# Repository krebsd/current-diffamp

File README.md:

# Differential current sense Amplifier - current-diffamp

Differential Amplifier circuit for use in current sensing applications. The circuit is designed to be used in conjunction with an oscilloscope.

## PREFACE
This project and especially its documentation including this README is still in a very early state of development. This document will be updated with further information in the future.

## EDA

* [KiCad](http://kicad-pcb.org) - KiCad EDA is used for the PCB design

## Authors

* **David Krebs** - *Initial work* - [krebsd](https://github.com/krebsd)

## License

<br />This work is licensed under a <a rel="license" href="http://creativecommons.org/licenses/by-sa/4.0/">Creative Commons Attribution-ShareAlike 4.0 International License</a>

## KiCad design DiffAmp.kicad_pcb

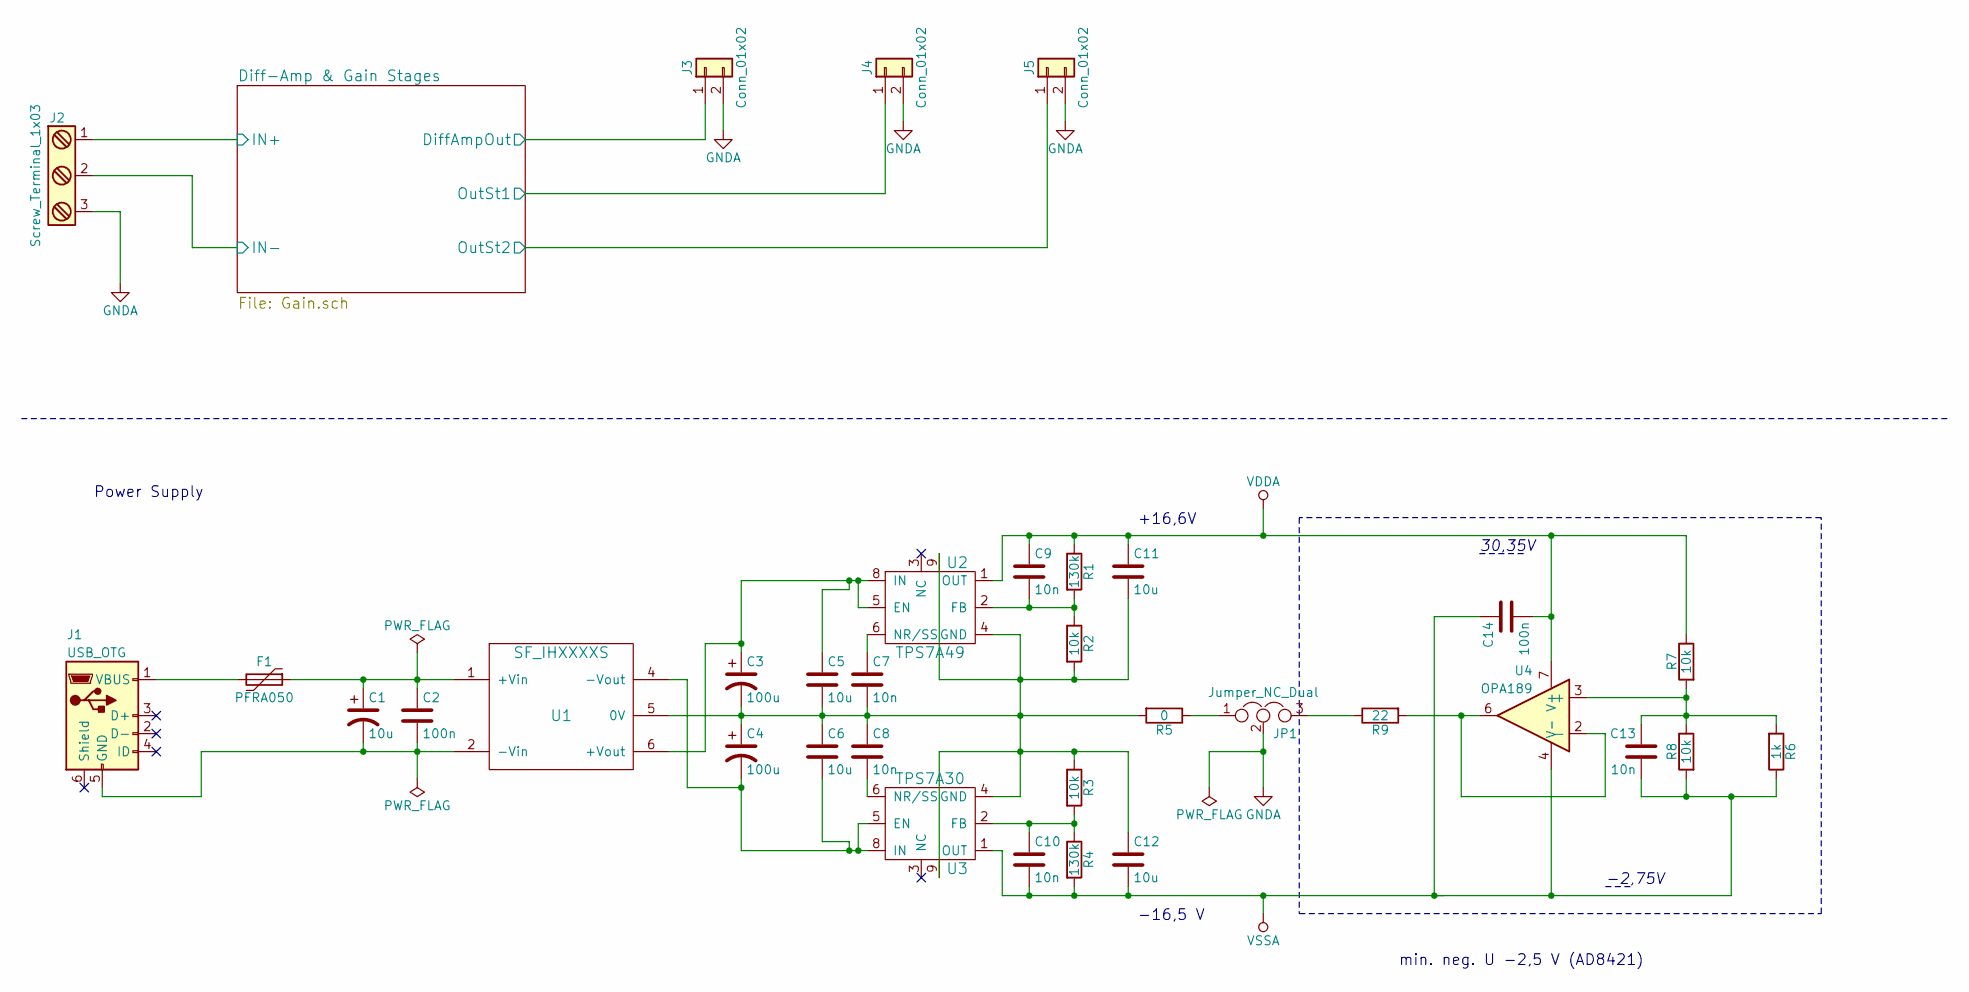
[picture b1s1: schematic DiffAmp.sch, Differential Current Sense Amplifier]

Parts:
C1: 10u; CP_Radial_D5.0mm_P2.00mm
C2, C14: 100n; C_0805
C3, C4: 100u; CP_Radial_D8.0mm_P3.50mm
C5, C6, C11, C12: 10u; C_1210
C7, C8, C9, C10, C13: 10n; C_0805
F1: PFRA050; R_Axial_DIN0204_L3.6mm_D1.6mm_P5.08mm_Horizontal
J1: USB_OTG; MIC_USB_BBU
J2: Screw_Terminal_1x03; TerminalBlock_bornier-3_P5.08mm
J3, J4, J5: Conn_01x02; Pin_Header_Straight_1x02_Pitch2.54mm
JP1: Jumper_NC_Dual; Pin_Header_Straight_1x03_Pitch2.54mm
R1, R4: 130k; R_0805
R2, R3, R7, R8: 10k; R_0805
R5: 0; R_0805
R6: 1k; R_0805
R9: 22; R_0805
U1: SF_IHXXXXS; DCDC-Conv_TRACO_TMR_1-xxxx_Dual
U2: TPS7A49; MSOP-8-1EP_3x3mm_Pitch0.65mm
U3: TPS7A30; MSOP-8-1EP_3x3mm_Pitch0.65mm
U4: OPA189; SOIC-8_3.9x4.9mm_Pitch1.27mm

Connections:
/Diff-Amp & Gain Stages/DiffAmpOut: J3.1; also elsewhere on the board
/Diff-Amp & Gain Stages/IN+: J2.1; also elsewhere on the board
/Diff-Amp & Gain Stages/IN-: J2.2; also elsewhere on the board
/Diff-Amp & Gain Stages/OutSt1: J4.1; also elsewhere on the board
/Diff-Amp & Gain Stages/OutSt2: J5.1; also elsewhere on the board
GNDA: J2.3, J3.2, J4.2, J5.2, JP1.2; also elsewhere on the board
unnamed: C1.1, C2.1, F1.1, U1.1 (+Vin)
unnamed: C1.2, C2.2, J1.5 (GND), U1.2 (-Vin)
unnamed: C3.1, C5.1, U1.6 (+Vout), U2.5 (EN), U2.8 (IN)
unnamed: C4.2, C6.2, U1.4 (-Vout), U3.5 (EN), U3.8 (IN)
unnamed: C7.1, U2.6 (NR/SS)
unnamed: C8.2, U3.6 (NR/SS)
unnamed: C9.2, R1.2, R2.1, U2.2 (FB)
unnamed: C10.1, R3.2, R4.1, U3.2 (FB)
unnamed: C3.2, C4.1, C5.2, C6.1, C7.2, C8.1, C11.2, C12.1, R2.2, R3.1, R5.2, U1.5 (0V), U2.4 (GND), U2.9, U3.4 (GND), U3.9
unnamed: C13.1, R6.2, R7.2, R8.1, U4.3 (+)
unnamed: F1.2, J1.1 (VBUS)
unnamed: JP1.1, R5.1
unnamed: JP1.3, R9.1
unnamed: R9.2, U4.2 (-), U4.6
VDDA: C9.1, C11.1, C14.2, R1.1, R7.1, U2.1 (OUT), U4.7 (V+); also elsewhere on the board
VSSA: C10.2, C12.2, C13.2, C14.1, R4.2, R6.1, R8.2, U3.1 (OUT), U4.4 (V-); also elsewhere on the board

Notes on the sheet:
-16,5 V
+16,6V
-2,75V
30,35V
min. neg. U -2,5 V (AD8421)
Power Supply

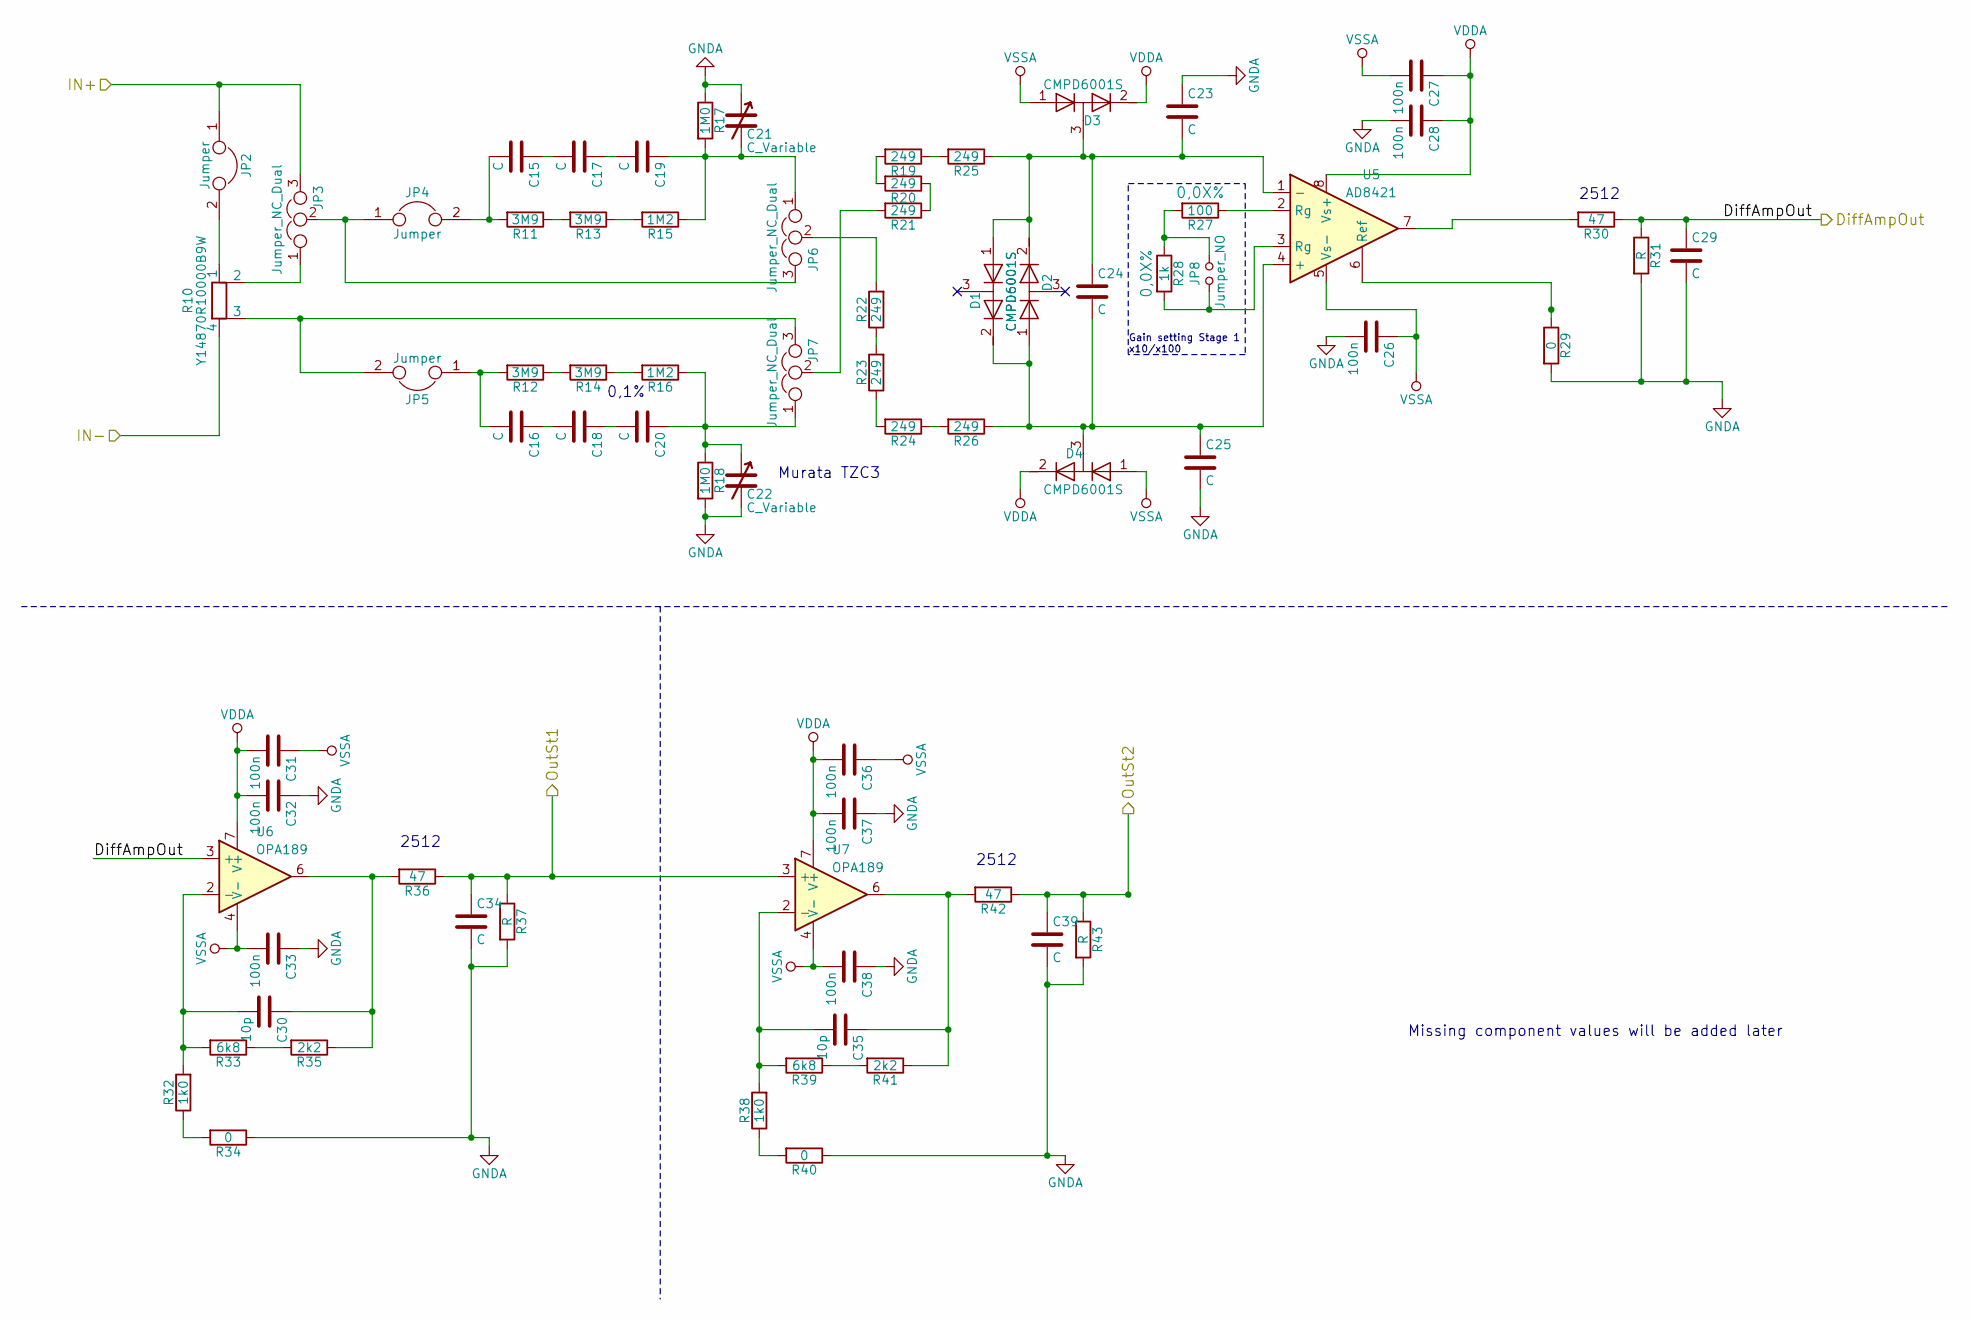
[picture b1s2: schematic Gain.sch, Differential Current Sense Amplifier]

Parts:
C15, C16, C17, C18, C19, C20, C23, C24, C25, C29, C34, C39: C; C_0805
C21, C22: C_Variable; C_Trimmer_Murata_TZC3
C26, C27, C28, C31, C32, C33, C36, C37, C38: 100n; C_0805
C30, C35: 10p; C_0805
D1, D2, D3, D4: CMPD6001S; SOT-23
JP2, JP4, JP5: Jumper; Pin_Header_Straight_1x02_Pitch2.54mm
JP3, JP6, JP7: Jumper_NC_Dual; Pin_Header_Straight_1x03_Pitch2.54mm
JP8: Jumper_NO; Pin_Header_Straight_1x02_Pitch2.54mm
R10: Y14870R10000B9W; CSM2512
R11, R12, R13, R14: 3M9; R_0805
R15, R16: 1M2; R_0805
R17, R18: 1M0; R_0805
R19, R20, R21, R22, R23, R24, R25, R26: 249; R_0805
R27: 100; R_0805; Toleranz 0,0X%
R28: 1k; R_0805; Toleranz 0,0X%
R29, R34, R40: 0; R_0805
R30, R36, R42: 47; R_2512
R31, R37, R43: R; R_0805
R32, R38: 1k0; R_0805
R33, R39: 6k8; R_0805
R35, R41: 2k2; R_0805
U5: AD8421; SOIC-8_3.9x4.9mm_Pitch1.27mm
U6, U7: OPA189; SOIC-8_3.9x4.9mm_Pitch1.27mm

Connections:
/Diff-Amp & Gain Stages/DiffAmpOut: C29.1, R30.1, R31.1, U6.3 (+); also elsewhere on the board
/Diff-Amp & Gain Stages/IN+: JP2.1, JP3.3; also elsewhere on the board
/Diff-Amp & Gain Stages/IN-: R10.4; also elsewhere on the board
/Diff-Amp & Gain Stages/OutSt1: C34.1, R36.1, R37.1, U7.3 (+); also elsewhere on the board
/Diff-Amp & Gain Stages/OutSt2: C39.1, R42.1, R43.1; also elsewhere on the board
GNDA: C21.1, C22.2, C23.1, C25.2, C26.2, C28.2, C29.2, C32.1, C33.1, C34.2, C37.1, C38.1, C39.2, R17.1, R18.2, R29.2, R31.2, R34.1, R37.2, R40.1, R43.2; also elsewhere on the board
unnamed: C15.1, C17.2
unnamed: C15.2, JP4.2, R11.2
unnamed: C16.1, C18.2
unnamed: C16.2, JP5.1, R12.2
unnamed: C17.1, C19.2
unnamed: C18.1, C20.2
unnamed: C19.1, C21.2, JP6.1, R15.1, R17.2
unnamed: C20.1, C22.1, JP7.1, R16.1, R18.1
unnamed: C23.2, C24.1, D1.1 (A), D2.2 (K), D3.3 (common), R25.1, U5.1 (-)
unnamed: C24.2, C25.1, D1.2 (K), D2.1 (A), D4.3 (common), R26.1, U5.4 (+)
unnamed: C30.1, R35.1, R36.2, U6.6
unnamed: C30.2, R32.2, R33.2, U6.2 (-)
unnamed: C35.1, R41.1, R42.2, U7.6
unnamed: C35.2, R38.2, R39.2, U7.2 (-)
unnamed: JP2.2, R10.1
unnamed: JP3.1, R10.2
unnamed: JP3.2, JP4.1, JP6.3
unnamed: JP5.2, JP7.3, R10.3
unnamed: JP6.2, R22.2
unnamed: JP7.2, R21.2
unnamed: JP8.1, R28.2, U5.3 (Rg)
unnamed: JP8.2, R27.2, R28.1
unnamed: R11.1, R13.2
unnamed: R12.1, R14.2
unnamed: R13.1, R15.2
unnamed: R14.1, R16.2
unnamed: R19.1, R25.2
unnamed: R19.2, R20.2
unnamed: R20.1, R21.1
unnamed: R22.1, R23.2
unnamed: R23.1, R24.2
unnamed: R24.1, R26.2
unnamed: R27.1, U5.2 (Rg)
unnamed: R29.1, U5.6 (Ref)
unnamed: R30.2, U5.7
unnamed: R32.1, R34.2
unnamed: R33.1, R35.2
unnamed: R38.1, R40.2
unnamed: R39.1, R41.2
VDDA: C27.1, C28.1, C31.2, C32.2, C36.2, C37.2, D3.2 (K), D4.2 (K), U5.8 (Vs+), U6.7 (V+), U7.7 (V+); also elsewhere on the board
VSSA: C26.1, C27.2, C31.1, C33.2, C36.1, C38.2, D3.1 (A), D4.1 (A), U5.5 (Vs-), U6.4 (V-), U7.4 (V-); also elsewhere on the board

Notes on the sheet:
0,1%
2512
Gain setting Stage 1 x10/x100
Missing component values will be added later
Murata TZC3

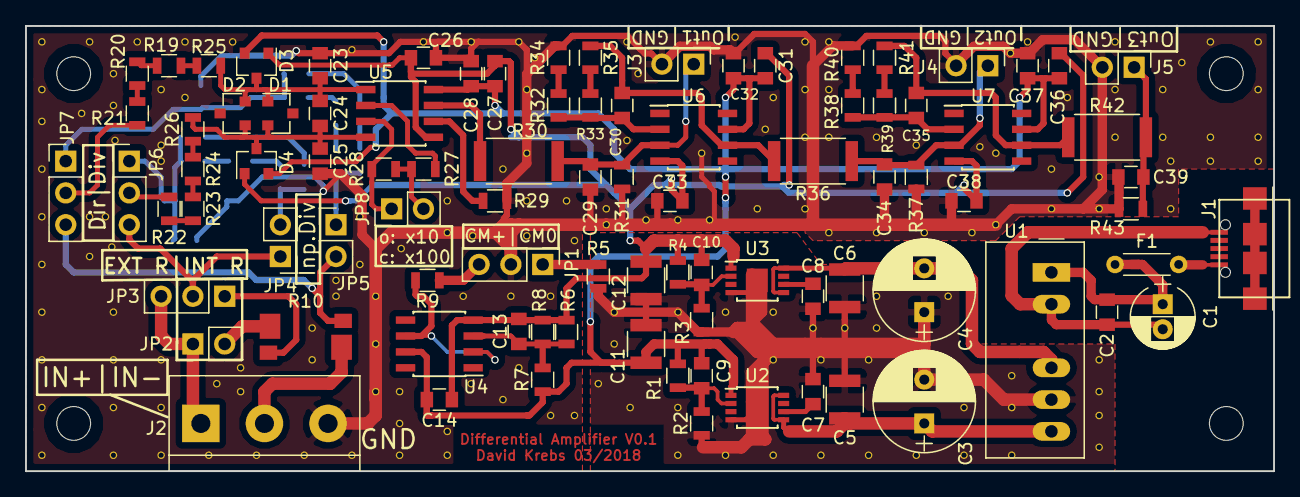
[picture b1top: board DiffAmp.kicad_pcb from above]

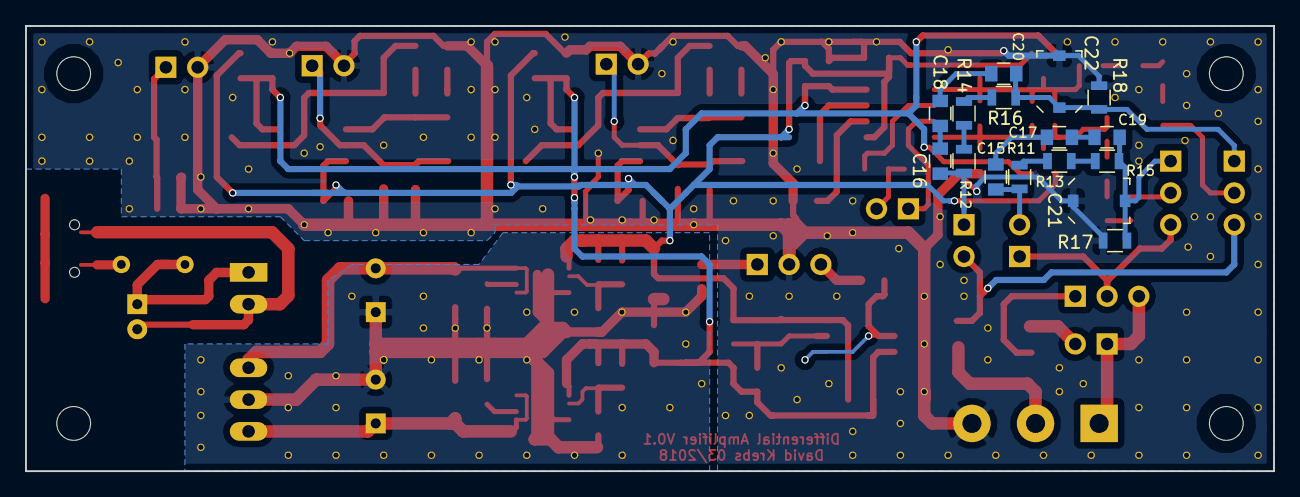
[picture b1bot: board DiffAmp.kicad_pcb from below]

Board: 2 copper layers, 99.7 x 35.6 mm, 107 parts (16 on the bottom side), 61 nets.

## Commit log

2018-03-14 Initial state of schematic
2018-03-16 Schematic rearranged Added Netlist
2018-03-16 Parts placed on PCB
2018-03-16 Corrected Board Outline
2018-03-16 Begin Layouting
2018-03-17 Layout Completed
2018-03-17 Silkscreen corrected
2018-03-17 Schematic pdf, Layout pdf + Gerber added
2018-03-17 Added preliminary component list
2018-03-18 Added PCB Assembly Drawing
2018-03-18 saved project footprints
2018-03-18 Changed GNDA-"Generation" on Schematic and Board
2018-03-18 Small modifications to layout - GND-Plane, VDD/VSS routing
2018-06-03 Update LICENSE
